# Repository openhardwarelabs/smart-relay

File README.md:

smart-relay
===========

Smart Relay with an integrated current sensor

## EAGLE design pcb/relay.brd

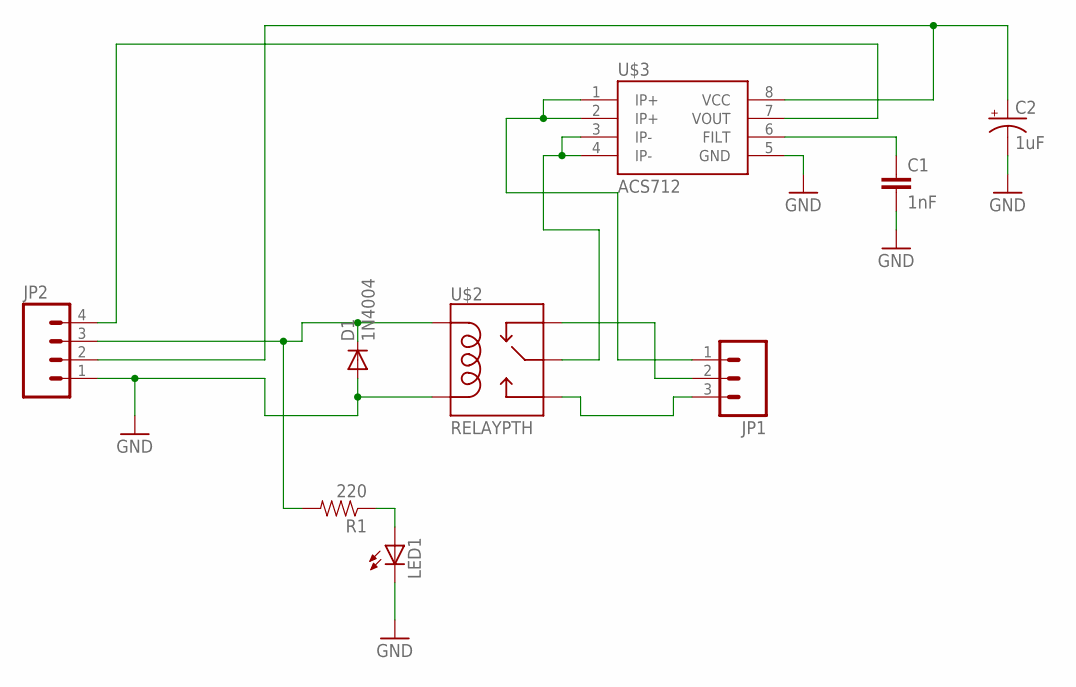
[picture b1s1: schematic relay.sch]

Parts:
C1: 1nF; CAP-PTH-SMALL-KIT
C2: 1uF; CPOL-RADIAL-10UF-25V
D1: 1N4004; DO41-10
JP1: M03SCREW; SCREWTERMINAL-3.5MM-3
JP2: M04PTH; 1X04
LED1: LED3MM
R1: 220; AXIAL-0.3
U$2: RELAYPTH; RELAY-G5Q
U$3: ACS712; SO08

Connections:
GND: C1.2, C2.2 (-), D1.A, JP2.1, LED1.K (C), U$2.1 (COIL2), U$3.5 (GND)
unnamed: LED1.A, R1.P$1 (1)
unnamed: D1.C, JP2.3, R1.P$2 (2), U$2.5 (COIL1)
unnamed: C1.1, U$3.6 (FILT)
unnamed: JP1.2, U$2.4 (NC)
unnamed: U$2.2 (MAIN), U$3.3 (IP-), U$3.4 (IP-)
unnamed: JP1.1, U$3.1 (IP+), U$3.2 (IP+)
unnamed: JP1.3, U$2.3 (NO)
unnamed: C2.1 (+), JP2.2, U$3.8 (VCC)
unnamed: JP2.4, U$3.7 (VOUT)

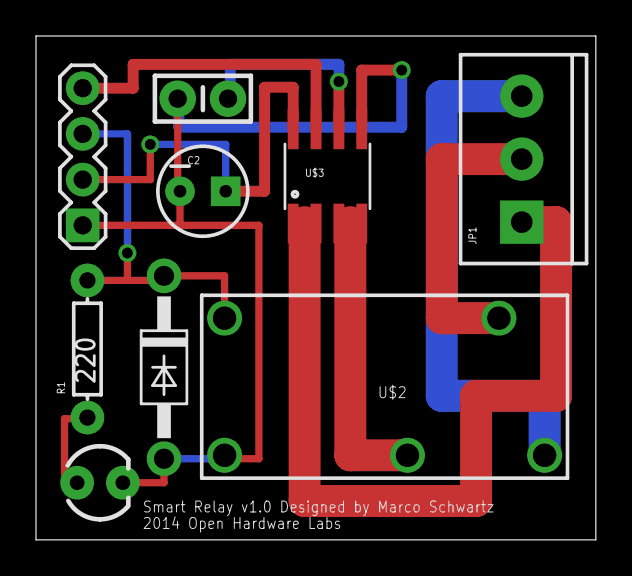
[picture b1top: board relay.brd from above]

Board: 2 copper layers, 31.1 x 28.0 mm, 9 parts (0 on the bottom side), 10 nets.

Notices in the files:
parts and their libraries:
SparkFun-Electromechanical: Licensing: CC v3.0 Share-Alike You are welcome to use this library for commercial purposes.
SparkFun-AnalogIC: Licensing:Creative Commons ShareAlike 4.0 International - https://creativecommons.org/licenses/by-sa/4.0
